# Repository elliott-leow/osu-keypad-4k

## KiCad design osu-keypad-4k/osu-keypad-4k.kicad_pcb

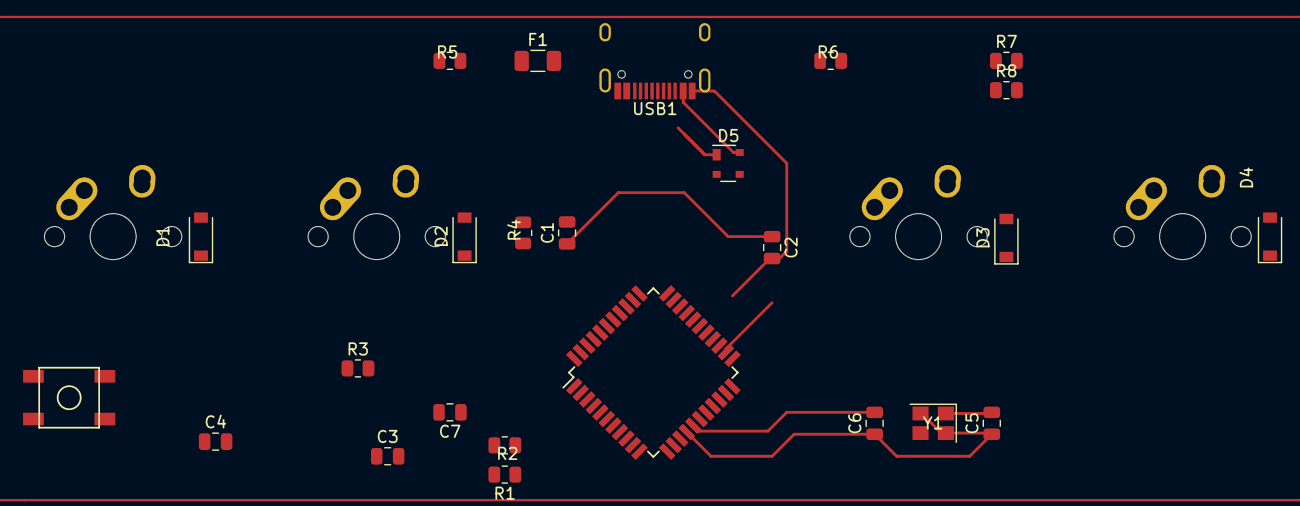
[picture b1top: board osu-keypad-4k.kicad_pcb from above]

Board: 2 copper layers, 29 parts (0 on the bottom side), 24 nets.

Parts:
C1, C2, C3: 0.1uF; C_0805_2012Metric
C4: 10uF; C_0805_2012Metric
C5, C6: 22pF; C_0805_2012Metric
C7: 1uF; C_0805_2012Metric
D1, D2, D3, D4: SOD-123; D_SOD-123
D5: PRTR5V0U2X; SOT-143
F1: 500m; Fuse_1206_3216Metric
MX1, MX2, MX3, MX4: MX-NoLED; MX-1U-NoLED
R1, R2, R7, R8: 22; R_0805_2012Metric
R3: R_Small; R_0805_2012Metric
R4: 10k; R_0805_2012Metric
R5, R6: 5.1k; R_0805_2012Metric
SW1: SW_Push; SKQG-1155865
U1: ATmega32U4-A; TQFP-44_10x10mm_P0.8mm
USB1: HRO-TYPE-C-31-M-12
Y1: 16MHz; Crystal_SMD_3225-4Pin_3.2x2.5mm

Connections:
+5V: C1.1, C2.1, C3.1, C4.1, F1.2, U1.2 (UVCC), U1.7 (VBUS), U1.14 (VCC), U1.24 (AVCC), U1.34 (VCC), U1.44 (AVCC)
COL0: MX1.1 (COL), MX2.1 (COL)
COL1: MX3.1 (COL), MX4.1 (COL)
D+: R2.1, R8.2
D-: R1.1, R7.2
GND: C1.2, C2.2, C3.2, C4.2, C5.1, C6.1, C7.2, D5.1 (GND), R4.2, R5.2, R6.2, SW1.1, U1.5 (UGND), U1.15 (GND), U1.23 (GND), U1.35 (GND), U1.43 (GND), USB1.1 (GND), USB1.12 (GND), USB1.13 (SHIELD), Y1.2, Y1.4
unnamed: C5.2, U1.17 (XTAL1), Y1.1
unnamed: C6.2, U1.16 (XTAL2), Y1.3
unnamed: C7.1, U1.6 (UCAP)
unnamed: D1.2 (A), MX1.2 (ROW)
unnamed: D2.2 (A), MX2.2 (ROW)
unnamed: D3.2 (A), MX3.2 (ROW)
unnamed: D4.2 (A), MX4.2 (ROW)
unnamed: D5.2 (I/O1), R8.1, USB1.8 (DP2)
unnamed: D5.3 (I/O2), R7.1, USB1.5 (DN2), USB1.6 (DP1), USB1.7 (DN1)
unnamed: R1.2, U1.3 (D-)
unnamed: R2.2, U1.4 (D+)
unnamed: R4.1, U1.33 (~HWB/PE2)
unnamed: R5.1, USB1.10 (CC2)
unnamed: R6.1, USB1.4 (CC1)
unnamed: SW1.2, U1.13 (~RESET)
ROW0: D1.1 (K), D3.1 (K)
ROW1: D2.1 (K), D4.1 (K)
VCC: D5.4 (VCC), F1.1, USB1.2 (VBUS), USB1.11 (VBUS)

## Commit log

2022-05-22 add submodules
2022-05-22 Footprint libs
2022-05-22 MCU schematic
2022-05-22 Finish Schematic
2022-05-23 start pcb
